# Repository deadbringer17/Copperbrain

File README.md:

# Copperbrain

Copperbrain is a local MCP server for safe KiCad 10 schematic/PCB analysis, deterministic
JLCPCB/LCSC sourcing, controlled changes, ERC/DRC validation, typed PCB design rules, and
component-only BOM estimates.

See this README for scope and public contracts, `docs/INSTALLATION.md` for setup, and
`docs/DEMO.md` for the reproducible reference flow.

## Installation

Requires Windows, Python 3.11 or newer, `uv`, and KiCad 10.x (`kicad-cli.exe` is discovered
dynamically). Controlled PCB routing uses a managed KiCadRoutingTools runtime with its
platform-specific Rust core; JLCImport and JLCPCB Tools are optional and enable local component
sourcing.

```powershell
git clone https://github.com/deadbringer17/Copperbrain.git
cd Copperbrain
uv sync --all-extras
uv run python scripts/setup_dependencies.py --skip-jlc-plugins
uv run pytest
```

Start the server with `uv run copperbrain`. Configure an MCP client to execute `uv` with arguments
`run copperbrain` and this repository as its working directory. Copperbrain exposes local stdio
only and never starts a public network listener. See `docs/INSTALLATION.md` for the full
environment-variable reference and mutation-safety details.

To update a source checkout explicitly from the official `origin/main`, run:

```powershell
uv run copperbrain update
```

The updater accepts only a clean `main` worktree with the official Copperbrain GitHub origin and
applies a Git fast-forward only. It refuses dirty worktrees, detached or different branches,
unexpected remotes, and divergent history; it never stashes, resets, rebases, or discards local
work. Restart Codex or open a new task after a successful update.

To fetch the pinned, hash-verified KiCadRoutingTools runtime and optional JLCImport/JLCPCB Tools integrations
automatically instead of installing them by hand, run:

```powershell
uv run python scripts/setup_dependencies.py
```

The script only ever contacts official sources over HTTPS (GitHub, Adoptium, `kicad.github.io`),
verifies a checksum whenever the source publishes one, and asks for confirmation before writing
anything — including the JLC plugins, which land in KiCad's own plugin directory, outside this
repository. See "Automated dependency setup" in `docs/INSTALLATION.md` for exactly what it does
and does not do.

## Installing in Codex CLI

Complete the installation above first. Codex (the `codex` CLI) reads MCP server definitions from
its `config.toml` — `~/.codex/config.toml` on Linux/macOS, `%USERPROFILE%\.codex\config.toml` on
Windows. Add a `[mcp_servers.copperbrain]` entry:

```toml
[mcp_servers.copperbrain]
command = "uv"
args = ["run", "--directory", "C:\\path\\to\\Copperbrain", "copperbrain"]
enabled = true
```

Codex launches `command` directly, without a shell and without setting a working directory of its
own, so `uv run` needs `--directory <repo>` instead of relying on `cd`; use the absolute path to
where you cloned this repository. To override an environment variable from
`docs/INSTALLATION.md#configuration` for this server only, add it under
`[mcp_servers.copperbrain.env]`, the same way other entries in `config.toml` do. Restart Codex (or
start a new session) after editing the file. Copperbrain still exposes local stdio only; registering
it this way adds no network exposure.

## Development

```powershell
uv sync --all-extras
uv run pytest
uv run ruff check .
uv run ruff format --check .
uv run mypy src
```

Run the stdio MCP server with `uv run copperbrain`.

Run the non-destructive offline demo with `uv run python scripts/run_demo.py`.

## Three acceptance gates

The public MCP exposes exactly three tools that accept a validated mutation:

1. `accept_schematic` for the project scaffold or schematic change set.
2. `accept_design_rules` for reviewed widths, clearances, vias, netclasses, and assignments.
3. `accept_pcb` for one aggregate placement, grounding, and routing change set prepared with
   `prepare_pcb_acceptance` and rechecked with `validate_pcb_acceptance`.

Granular PCB prepare/preview/validate/apply/rollback functions are internal and are not MCP tools.
They modify only the private aggregate workspace. `rollback_accepted_phase` is an explicit recovery
command, not another acceptance gate.

To start a new design safely, call `prepare_project_creation` with an existing parent directory
and a typed name/layer count. Copperbrain creates the schematic through `kicad-sch-api`, creates
the empty board through KiCad's bundled Python API, validates both files, and publishes only a
preview under `<new-project>/copperbrain-output/previews/schematic/`.
`accept_schematic` applies the validated scaffold; recovery remains hash guarded.

For an opened KiCad project, Copperbrain writes every deliverable artifact below
`<project>/copperbrain-output/`: at most the stable `schematic`, `design-rules`, and `pcb` previews
under `previews/`, plus BOM exports under `bom/`. Private mutation workspaces, caches, and rollback
snapshots are not placed in the project.

## Project analysis via MCP

Call `detect_kicad` to confirm KiCad, CLI, and JLC plugin availability, then `open_project` to
open a project read-only and hash its sources. `get_project_summary` returns sheets, components,
electrical nets, and power symbols; `analyze_schematic` returns deterministic, evidence-backed
observations; `trace_net` returns every pin KiCad assigns to one exact net name. `run_erc` and
`run_drc` run KiCad's checks and normalize violations without touching project files.

## Schematic changes via MCP

`prepare_schematic_change` stages allowlisted operations in a private workspace and returns a
semantic diff, risks, and a project-local PDF preview; `validate_change` revalidates it in place.
Applying requires the first acceptance gate, `accept_schematic`, with `confirmed=true` and
`editor_closed=true`.

## Component sourcing via MCP

`search_components` ranks JLCPCB/LCSC candidates against typed requirements using the installed
JLCPCB Tools catalog or a recorded `COPPERBRAIN_JLC_CATALOG`. `get_component_details` returns
normalized catalog details for one exact LCSC part; `compare_components` and `find_alternatives`
rank supplied or discovered candidates against the same requirements. `estimate_component_cost`
estimates component-only cost at one requested quantity. `import_component_assets` installs the
resolved symbol/footprint/3D/datasheet assets locally from allowlisted HTTPS sources.

## BOM via MCP

`generate_bom` groups and enriches the schematic BOM and writes JSON/CSV/Markdown under
`copperbrain-output/bom/`. `estimate_bom_cost` totals component-only cost at requested board
quantities; `suggest_bom_substitutions` proposes requirement-motivated alternatives for BOM lines.
All cost figures explicitly exclude PCB, assembly, stencil, shipping, taxes, and duties.

## PCB design rules via MCP

Use `analyze_pcb_constraints` to inspect current netclasses and receive evidence-backed net-role
suggestions. Pass reviewed fabrication limits and electrical intent to `propose_design_rules`,
then use `prepare_pcb_rule_change`, `validate_pcb_rule_change`, and
`accept_design_rules`. Applying requires the second acceptance and a saved, closed KiCad editor;
`rollback_accepted_phase` restores the phase snapshot when explicitly invoked.

`ManufacturingProfile` covers minimum clearance/track/via dimensions, copper thickness, allowed
temperature rise, and internal/external current layer. `NetRuleRequirement` covers exact net names,
role, current, voltage, explicit clearance/width, creepage, maximum routed length, and optional
differential geometry/maximum uncoupled length. Raw `.kicad_dru` text is never accepted through
MCP.

High-current rules require a current or reviewed width. High-voltage rules require reviewed
clearance. Differential geometry is explicitly marked as not impedance-controlled unless width
and gap are supplied from a verified stackup calculation.

Before proposing routing rules, Copperbrain resolves every connected footprint and measures its
electrical pads, minimum pitch, and edge-to-edge pad clearance. If a class width or clearance does
not fit the package, the generated `.kicad_dru` applies a narrower track width or reduced clearance
only inside that component's courtyard, never below the fabrication profile minimum. The original
class remains active outside the package. Missing project-local courtyards can be generated inside
the same previewed change set and are validated through KiCad CLI; unresolved footprints or
packages narrower than the fabrication minimum produce a safe refusal.

## PCB inspection and placement via MCP

Use `get_pcb_summary`, `inspect_pcb_net`, and `get_footprint_placement` for typed board queries.
`analyze_placement` reports conservative courtyard overlaps, footprints outside Edge.Cuts,
estimated ratsnest length, occupied envelope, compactness, side counts, and cross-layer nets.
`propose_component_placement` accepts exact references, a typed optional region, spacing/grid and
routing-corridor limits, plus deterministic `compact` or `grid`, rotation, and layer policies.
Compact placement scores pad connectivity and envelope growth, keeps connectors near edges, and
allows automatic bottom placement only for small SMD passives.

Pass the returned operations directly to `prepare_pcb_acceptance`. Placement is applied and
validated inside its private aggregate workspace without an intermediate PDF or published copy;
no separate placement preview or acceptance is exposed.

The official `kicad-python` IPC binding is installed and detected dynamically for live board
transactions. PCB inspection and safe preview do not require a running editor: the typed file
adapter and `kicad-cli` remain the deterministic offline path. No MCP placement tool accepts raw
KiCad S-expressions, and this extension does not route traces or modify zones, keepouts, or the
board outline.
Un cambio `F.Cu`/`B.Cu` viene eseguito soltanto nella copia temporanea attraverso l'API `pcbnew`
inclusa in KiCad, cosi pad, grafica, testi e modelli 3D vengono trasformati insieme. Preview, DRC,
conferma esplicita, snapshot e rollback restano obbligatori.

## Post-placement PCB grounding

Include the reviewed grounding request in `prepare_pcb_acceptance`. It targets every
pad in one or more reviewed ground domains and derives all zone outlines from the real closed
`Edge.Cuts`, pad geometry, fanouts, and vias. The default is always a two-copper-layer board:
`PGND` owns the main shaped region on `F.Cu`, while `GND` owns the main shaped region on `B.Cu`.
Planner-derived local regions on the opposite side are cut out of the main region with explicit
clearance and distinct priorities. A four-layer stackup is used only when
`copper_layers=4` is explicitly requested; that opt-in policy uses `PGND -> F.Cu/In2.Cu` and
`GND -> In1.Cu/B.Cu` for an unambiguous pair.

The domains remain distinct KiCad nets and are connected only through two-terminal bridges such as
a 0-ohm resistor or net tie explicitly named in `bridge_references`. Pads that do not touch their
assigned plane receive
typed, clearance-screened pad-to-via fanouts. `thermal` and `solid` pad connections are selectable
per domain; local shaped regions are solid and power ground commonly uses `solid`. Via-in-pad is opt-in because it requires a reviewed
fabrication process. Existing selected-net zones are replaced only when
`replace_existing_planes=true` is explicitly requested.

The result is validated inside the private aggregate workspace without a grounding preview. The
KiCad Project Manager may remain open: only a PCB document lock blocks the final aggregate
mutation. `rollback_accepted_phase` restores the aggregate PCB snapshot. Ambiguous
domain roles, overlapping layer assignments, missing/ambiguous bridges, unsafe fanouts, or new DRC
errors cause a structured refusal.
The workflow does not accept polygons or KiCad expressions from callers, and it does not claim
thermal, return-path, EMC, SI/PI, stackup, or DFM certification.

## Headless PCB initialization via MCP

For an empty board, the internal layout composer accepts a typed rectangular outline, one
placement for every physical schematic footprint, optional fixed M3 mounting holes, and explicit
footprint overrides. It synchronizes footprints, builds the unrouted PCB, and runs comparative
ERC/DRC and placement analysis inside the aggregate workspace without publishing an intermediate
preview. There is no separate layout preview or acceptance.

The bounded `test_bench_pico` reference helper demonstrates this flow for a provisional 12 V,
20 A brushed-DC H-bridge using DRV8701, four external 60 V MOSFETs, ATtiny1616, half-duplex
RS-485, and four protected 5–24 V digital sensor inputs. Its typed plan uses a compact 120 x 100 mm board,
four M3 holes, a star-separated `PGND`/logic `GND`, and a 70 um external-copper assumption. It is
a review benchmark, not a production-qualified design; high-current zones, thermal/EMC/DFM,
motor stall behavior, and the final stackup still require engineering validation.

The `benchmark_bldc_drv8311` reference project exercises the same guarded workflow on an
85 x 50 mm four-layer BLDC driver. It uses a DRV8311S integrated three-phase stage for a
provisional 9--12.6 V, 2 A continuous operating point, exposes 6-PWM, SPI, three current-sense
outputs, fault, and Hall signals, and includes input protection, decoupling, a reviewed In1.Cu GND
plane, thermal-pad via-in-pad fanout, and project-local rule classes. The generated BOM and design
report live below `benchmark_bldc_drv8311/copperbrain-output/`. It remains a benchmark, not a
production release: power/phase copper, thermal/SOA, EMC, DFM, and the remaining signal routing are
explicitly blocked by readiness evidence rather than being silently inferred.

## Controlled PCB routing via MCP

After rules and placement/grounding intent are reviewed, use `analyze_unrouted_nets`
to identify the remaining disconnected pad groups. Ground-zone connectivity is included, so the
router does not redundantly route pads already joined by an applied plane. Check
`get_routing_backend_status`, then call `propose_pcb_routing`. KiCadRoutingTools runs locally through
its Python CLI and Rust-accelerated A* core. Copperbrain can run at most three isolated ordering
strategies: `mps`, `inside_out`, and `original`. One candidate is used by default and a request for
a fourth is rejected. Copperbrain ranks candidates by completion, new DRC errors, open connections,
vias, and routed length. Only the selected candidate's copper delta becomes typed segments and vias;
there is no internal routing fallback. Reviewed planes remain on the private input board as copper
obstacles, while their nets are excluded from the explicit signal-routing batch. The selected typed
copper is applied to the already-grounded private board, followed by KiCad zone refill and
comparative DRC.
Fine-pitch escape geometry is opt-in per routing batch. When enabled, Copperbrain derives short
typed stubs from pad and courtyard geometry and, for a nearby opposite-side target, a clearance-
offset dogbone via with an outside-courtyard approach. It includes these seeds in the private router
input and subjects the resulting complete copper delta to the same scope, preservation,
connectivity, and DRC gates.
When `nets` is empty, Copperbrain materializes the exact currently-unrouted net set before starting
the backend. KiCadRoutingTools receives those exact names through its fixed `--nets` argument;
non-target nets, existing routes, planes, keepouts, pads, and the board outline remain obstacles.
Copperbrain never enables the backend option that permits ripping pre-existing routes. Every result
is rejected if it removes existing copper or adds copper outside the requested net set.

Pass the reviewed routing requests with placement and grounding to `prepare_pcb_acceptance`.
Copperbrain stops after the bounded candidate comparison, applies only the best candidate to the
private prepared PCB, refills zones, rechecks connectivity, and runs comparative DRC inside one
private workspace without routing previews. It does not keep retrying to obtain a complete route.
Final engineering cleanup and the explicit decision to apply the prepared PCB remain with the
user. Only the complete aggregate publishes
`copperbrain-output/previews/pcb/` and can be applied by `accept_pcb` with the third acceptance and
a closed editor. The KiCad Project Manager may remain open; only a PCB-document lock blocks the
aggregate apply/rollback. Boards containing pre-existing copper are rejected by default; explicitly select the
`preserve` policy only for intentional incremental routing. Wall-time and output-stall watchdogs
stop the complete router process tree. The typed delta is always applied to the original-precision
project copy.
Each proposal writes versioned baseline and per-candidate JSON metrics below the private
`COPPERBRAIN_DATA_DIR/metrics/connectivity/` tree. KiCadRoutingTools attempt records retain bounded
queued/routed/failure counts, duration, routed copper, watchdog evidence, and resource data when the
backend exposes it. Backend output is bounded and sensitive net names are replaced with hashes. The returned
`RoutingPlan.metrics_run_id` correlates those records with preview, apply, and recovery.
Call `get_connectivity_metrics` with that ID for a bounded, sanitized optimization view including
the best observed pass, connection delta, failed-candidate count, stagnation, and watchdog causes.
New records use schema 5 while the reader remains compatible with persisted schema-2 records.

For the compact end-to-end surface, call `prepare_pcb_acceptance`, review its preview, then use
`validate_pcb_acceptance` and `accept_pcb`. `assess_pcb_readiness` intentionally keeps
`production_ready=false` when DFM, stackup,
thermal, SI/PI, EMC, or impedance checks have not been performed, even if routing/ERC/DRC pass.

The AI may explain and review the structured candidate evidence, but it cannot override
connectivity, DRC, confirmation, stale-hash, or editor-state gates. This workflow does not certify
impedance, SI/PI/EMC, thermal behavior, or regulatory compliance. Raw KiCad expressions, zones,
and keepouts remain unavailable through the routing tools.

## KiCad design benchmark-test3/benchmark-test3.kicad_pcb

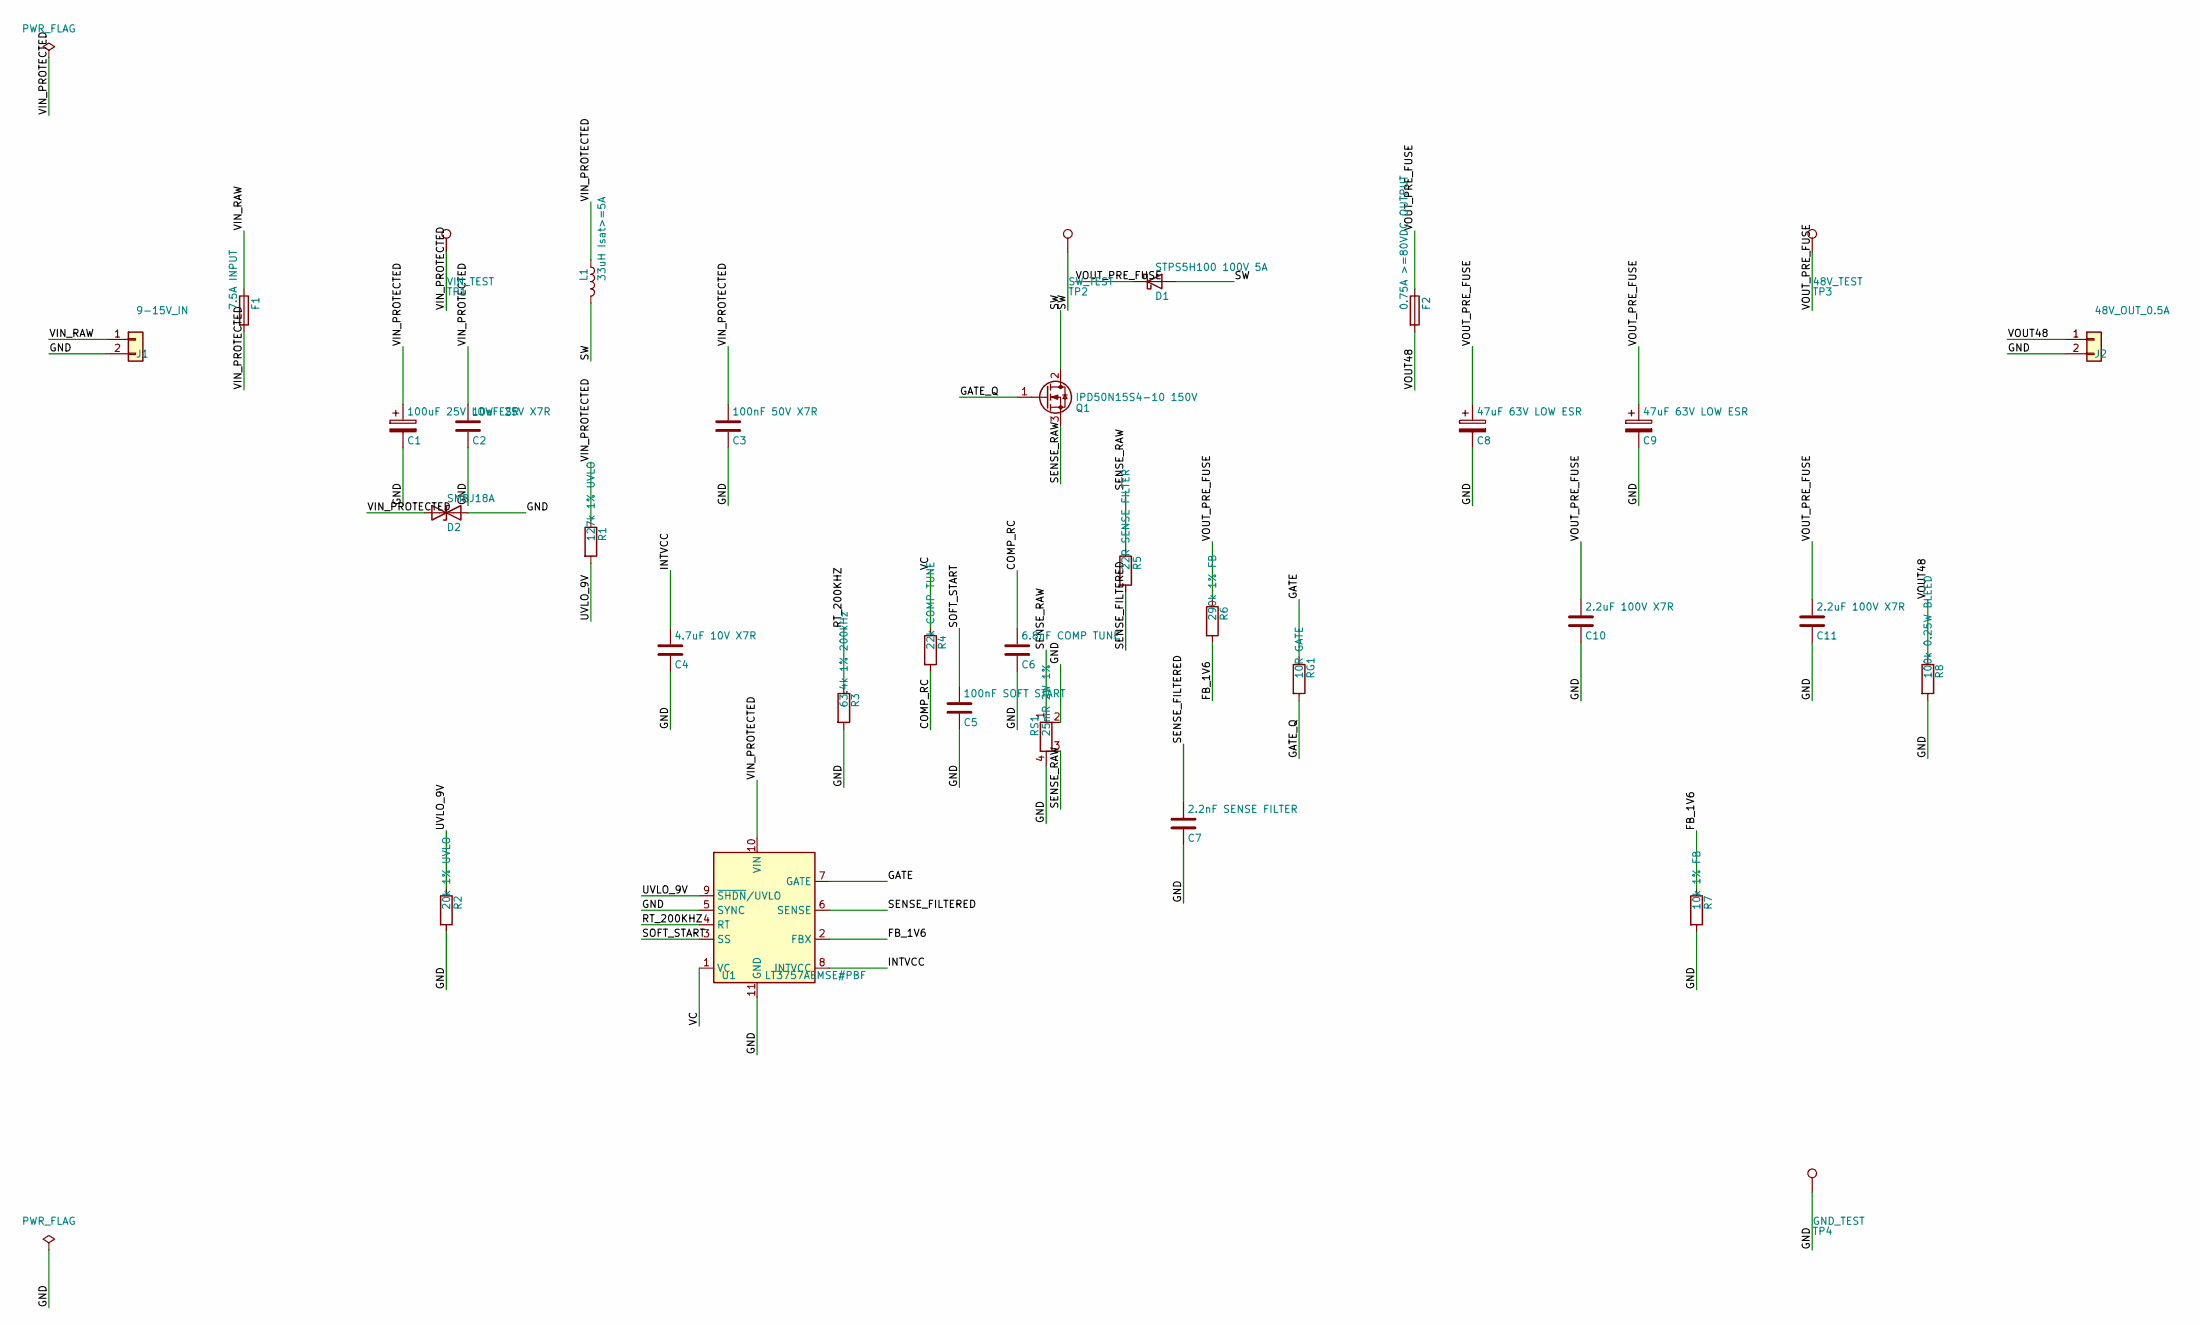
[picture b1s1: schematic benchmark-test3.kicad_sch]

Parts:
C1: 100uF 25V LOW ESR; CP_Elec_8x10
C2: 10uF 25V X7R; C_1210_3225Metric
C3: 100nF 50V X7R; C_0805_2012Metric
C4: 4.7uF 10V X7R; C_0805_2012Metric
C5: 100nF SOFT START; C_0603_1608Metric
C6: 6.8nF COMP TUNE; C_0603_1608Metric
C7: 2.2nF SENSE FILTER; C_0603_1608Metric
C8, C9: 47uF 63V LOW ESR; CP_Elec_10x10.5
C10, C11: 2.2uF 100V X7R; C_1210_3225Metric
D1: STPS5H100 100V 5A; TO-252-3_TabPin2
D2: SMBJ18A; D_SMB
F1: 7.5A INPUT; Fuse_1812_4532Metric
F2: 0.75A >=80VDC OUTPUT; Fuse_1206_3216Metric
J1: 9-15V_IN; TerminalBlock_MaiXu_MX126-5.0-02P_1x02_P5.00mm
J2: 48V_OUT_0.5A; TerminalBlock_MaiXu_MX126-5.0-02P_1x02_P5.00mm
L1: 33uH Isat>=5A; L_Coilcraft_MSS1260-XXX
Q1: IPD50N15S4-10 150V; TO-252-3_TabPin2
R1: 127k 1% UVLO; R_0805_2012Metric
R2: 20k 1% UVLO; R_0805_2012Metric
R3: 63.4k 1% 200kHz; R_0603_1608Metric
R4: 22k COMP TUNE; R_0603_1608Metric
R5: 22R SENSE FILTER; R_0603_1608Metric
R6: 290k 1% FB; R_0805_2012Metric
R7: 10k 1% FB; R_0805_2012Metric
R8: 100k 0.25W BLEED; R_1206_3216Metric
RG1: 10R GATE; R_0603_1608Metric
RS1: 25mR 2W 1%; R_Shunt_Vishay_WSK2512_6332Metric_T2.21mm
TP1: VIN_TEST; TestPoint_Plated_Hole_D2.0mm
TP2: SW_TEST; TestPoint_Plated_Hole_D2.0mm
TP3: 48V_TEST; TestPoint_Plated_Hole_D2.0mm
TP4: GND_TEST; TestPoint_Plated_Hole_D2.0mm
U1: LT3757AEMSE#PBF; MSOP-10-1EP_3x3mm_P0.5mm_EP1.68x1.88mm; MPN LT3757AEMSE#PBF

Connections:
/COMP_RC: C6.1, R4.2
/FB_1V6: R6.2, R7.1, U1.2 (FBX)
/GATE: RG1.1, U1.7 (GATE)
/GATE_Q: Q1.1 (G), RG1.2
/GND: C1.2, C2.2, C3.2, C4.2, C5.2, C6.2, C7.2, C8.2, C9.2, C10.2, C11.2, D2.2 (A2), J1.2, J2.2, R2.2, R3.2, R7.2, R8.2, RS1.2, RS1.4, TP4.1, U1.5 (SYNC), U1.11 (GND)
/INTVCC: C4.1, U1.8 (INTVCC)
/RT_200KHZ: R3.1, U1.4 (RT)
/SENSE_FILTERED: C7.1, R5.2, U1.6 (SENSE)
/SENSE_RAW: Q1.3 (S), R5.1, RS1.1, RS1.3
/SOFT_START: C5.1, U1.3 (SS)
/SW: D1.2 (A), L1.2, Q1.2 (D), TP2.1
/UVLO_9V: R1.2, R2.1, U1.9 (~SHDN/UVLO)
/VC: R4.1, U1.1 (VC)
/VIN_PROTECTED: C1.1, C2.1, C3.1, D2.1 (A1), F1.2, L1.1, R1.1, TP1.1, U1.10 (VIN)
/VIN_RAW: F1.1, J1.1
/VOUT48: F2.2, J2.1, R8.1
/VOUT_PRE_FUSE: C8.1, C9.1, C10.1, C11.1, D1.1 (K), F2.1, R6.1, TP3.1

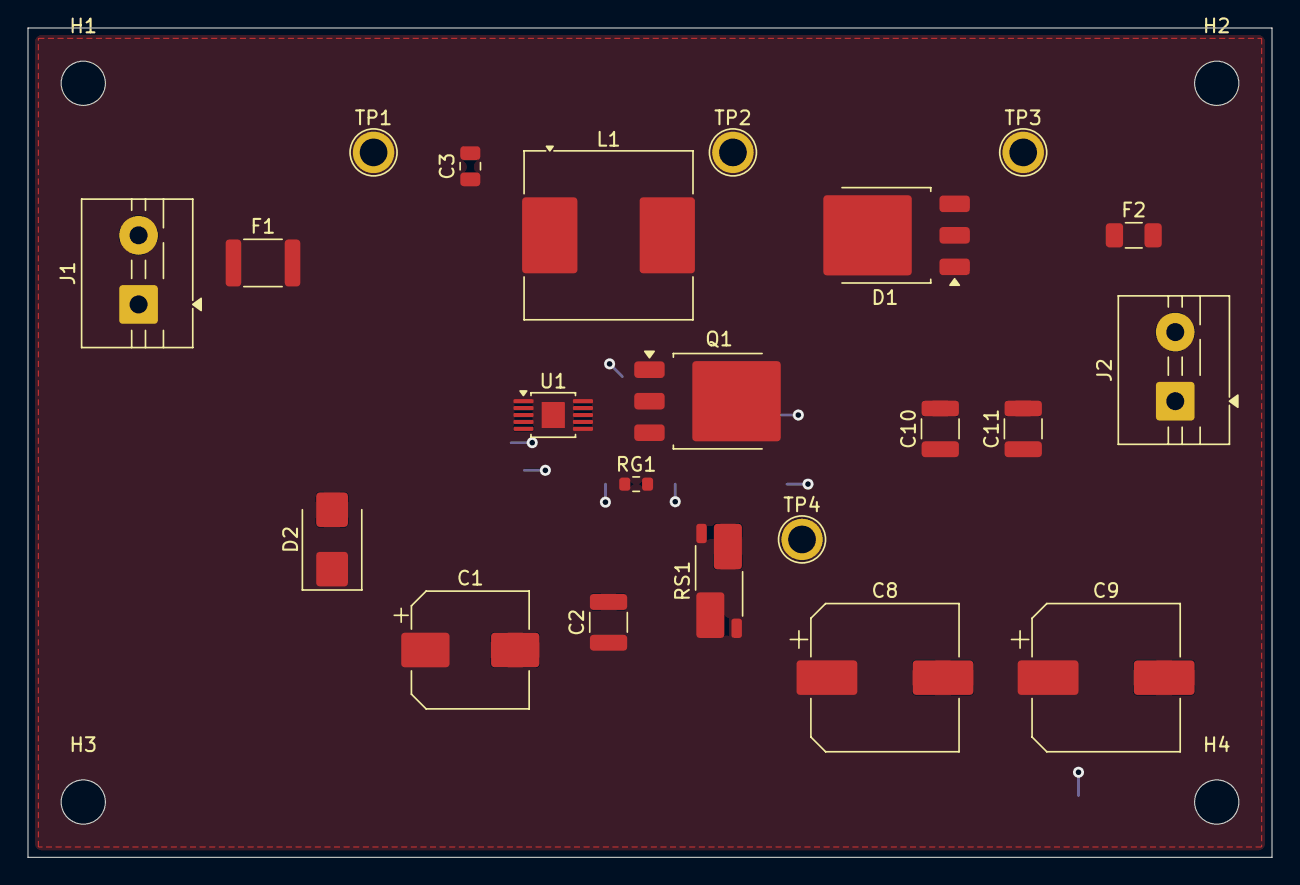
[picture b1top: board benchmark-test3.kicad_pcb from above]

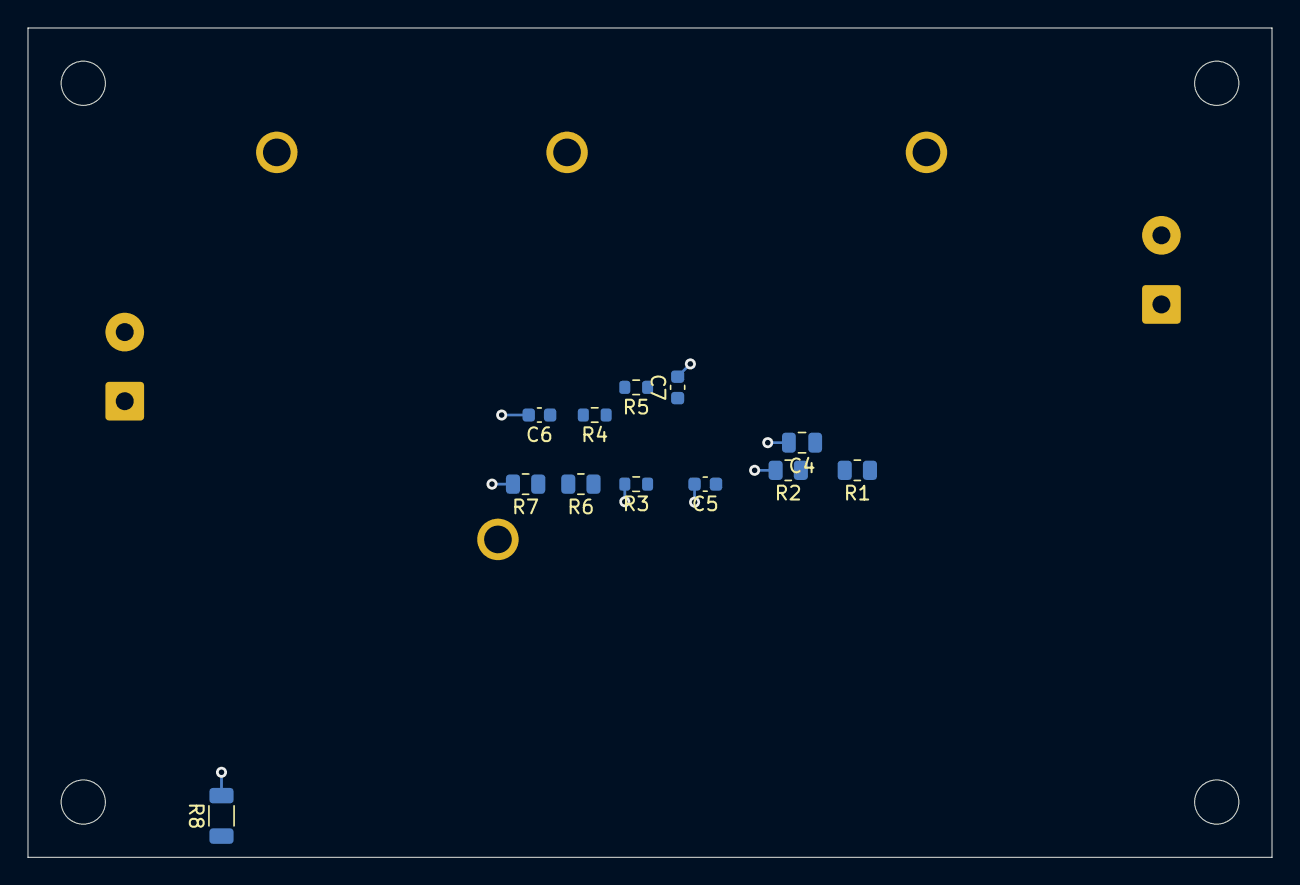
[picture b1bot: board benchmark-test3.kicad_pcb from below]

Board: 2 copper layers, 90.0 x 60.0 mm, 38 parts (12 on the bottom side), 17 nets.

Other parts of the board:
H1, H2, H3, H4: MountingHole_3.2mm_M3

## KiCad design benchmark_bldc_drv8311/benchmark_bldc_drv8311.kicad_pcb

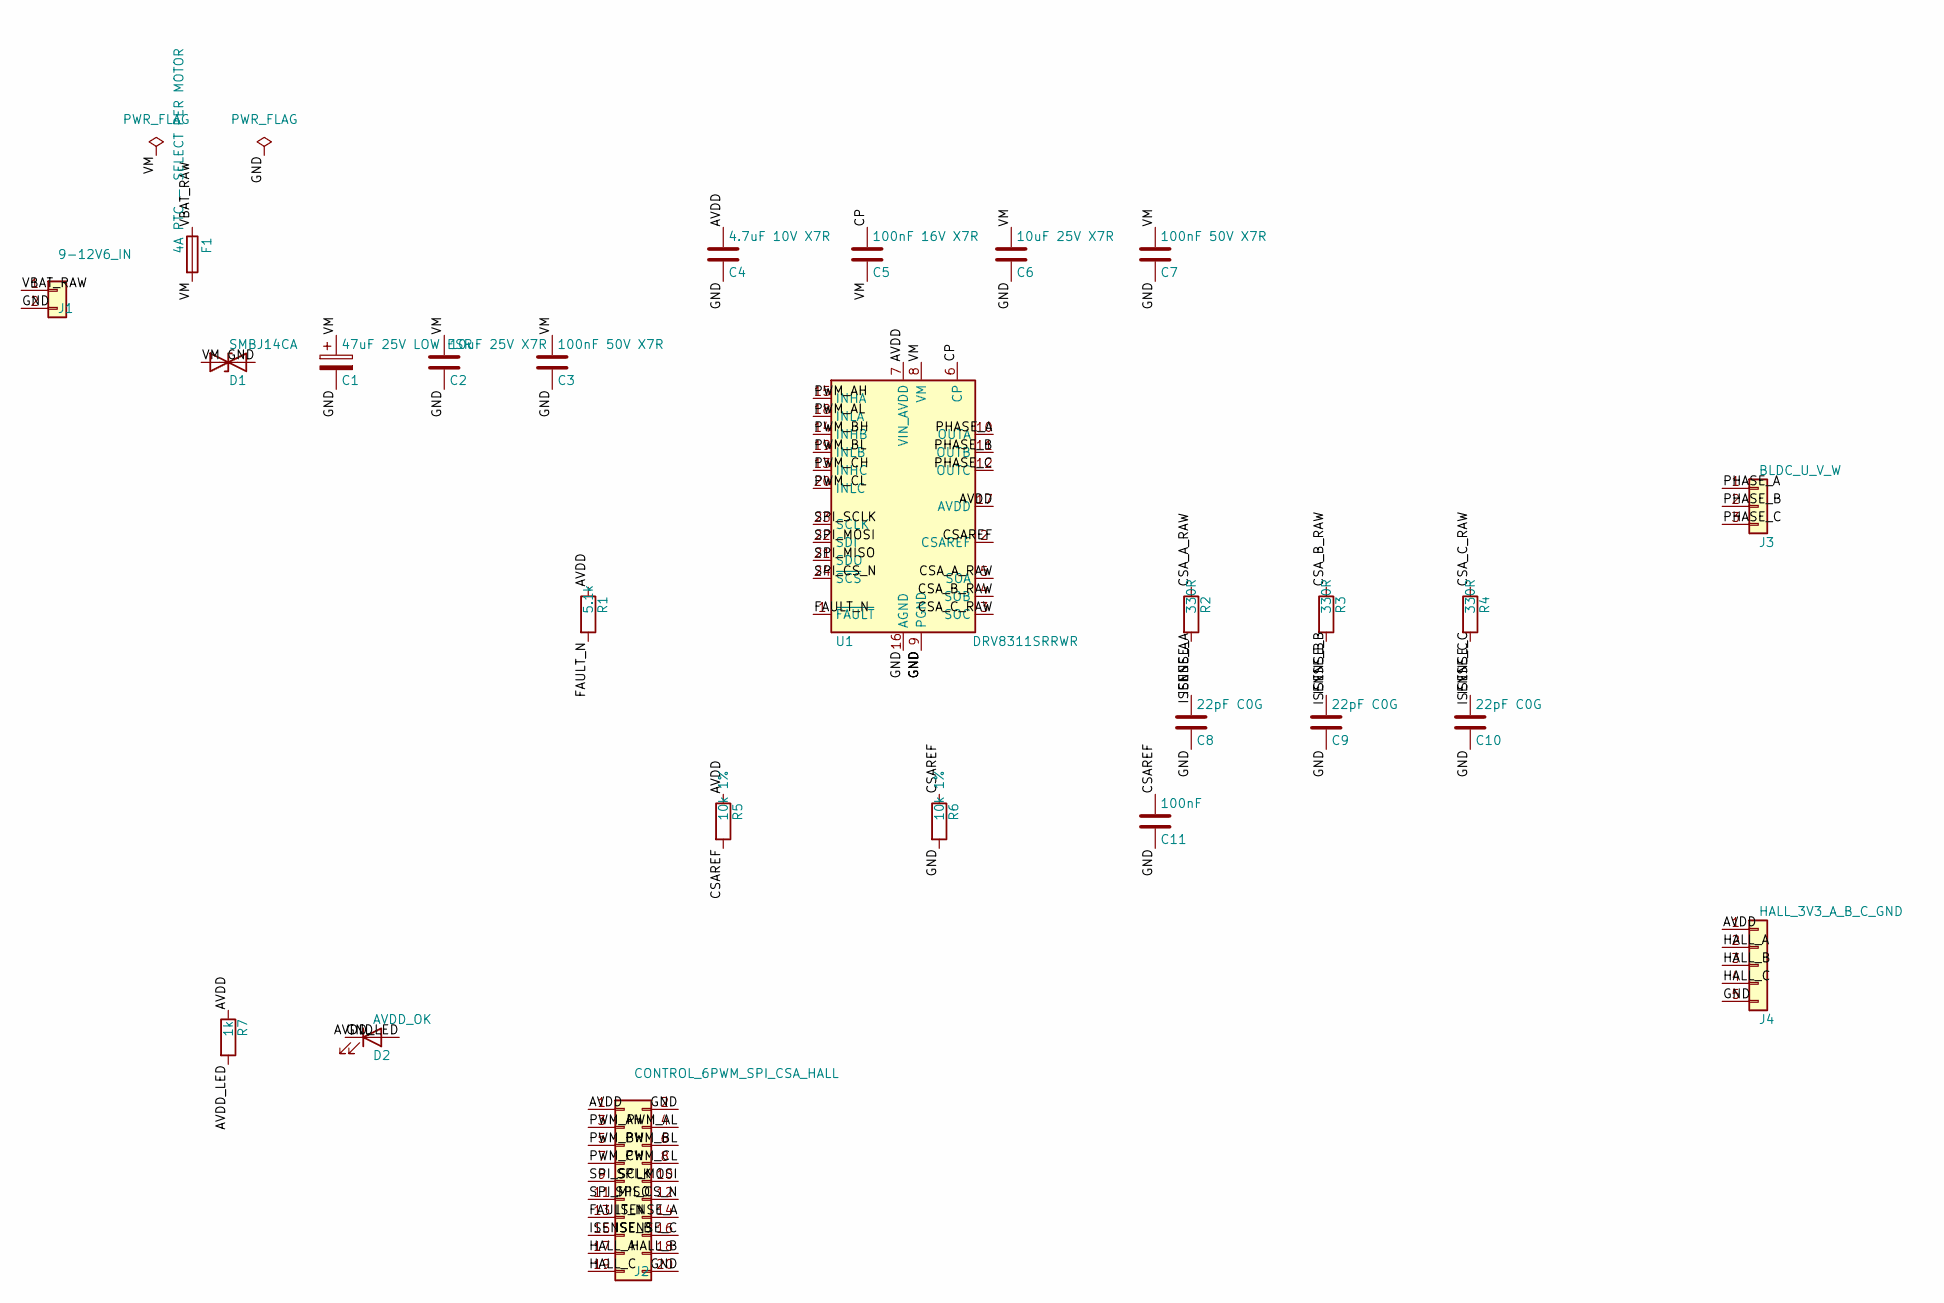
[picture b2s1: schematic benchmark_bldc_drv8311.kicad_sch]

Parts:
C1: 47uF 25V LOW ESR; CP_Radial_D8.0mm_P3.50mm
C2, C6: 10uF 25V X7R; C_1206_3216Metric
C3, C7: 100nF 50V X7R; C_0603_1608Metric
C4: 4.7uF 10V X7R; C_0805_2012Metric
C5: 100nF 16V X7R; C_0603_1608Metric
C8, C9, C10: 22pF C0G; C_0603_1608Metric
C11: 100nF; C_0603_1608Metric
D1: SMBJ14CA; D_SMB; MPN SMBJ14CA; LCSC C151253
D2: AVDD_OK; LED_0603_1608Metric
F1: 4A PTC - SELECT PER MOTOR; Fuse_1812_4532Metric_Pad1.30x3.40mm_HandSolder
J1: 9-12V6_IN; TerminalBlock_MaiXu_MX126-5.0-02P_1x02_P5.00mm
J2: CONTROL_6PWM_SPI_CSA_HALL; PinHeader_2x10_P1.27mm_Vertical
J3: BLDC_U_V_W; TerminalBlock_MaiXu_MX126-5.0-03P_1x03_P5.00mm
J4: HALL_3V3_A_B_C_GND; JST_PH_B5B-PH-K_1x05_P2.00mm_Vertical
R1: 5.1k; R_0603_1608Metric
R2, R3, R4: 330R; R_0603_1608Metric
R5, R6: 10k 1%; R_0603_1608Metric
R7: 1k; R_0603_1608Metric
U1: DRV8311SRRWR; Texas_RRW0024A_WQFN-24-1EP_3x3mm_P0.4mm_EP1.9x1.9mm; MPN DRV8311SRRWR; LCSC UNSOURCED

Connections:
/AVDD: C4.1, J2.1, J4.1, R1.1, R5.1, R7.1, U1.7 (VIN_AVDD), U1.17 (AVDD)
/AVDD_LED: D2.2 (A), R7.2
/CP: C5.1, U1.6 (CP)
/CSAREF: C11.1, R5.2, R6.1, U1.2 (CSAREF)
/CSA_A_RAW: R2.1, U1.5 (SOA)
/CSA_B_RAW: R3.1, U1.4 (SOB)
/CSA_C_RAW: R4.1, U1.3 (SOC)
/FAULT_N: J2.13, R1.2, U1.1 (~FAULT)
/GND: C1.2, C2.2, C3.2, C4.2, C6.2, C7.2, C8.2, C9.2, C10.2, C11.2, D1.2 (A2), D2.1 (K), J1.2, J2.2, J2.20, J4.5, R6.2, U1.9 (PGND), U1.16 (AGND), U1.25 (PGND)
/HALL_A: J2.17, J4.2
/HALL_B: J2.18, J4.3
/HALL_C: J2.19, J4.4
/ISENSE_A: C8.1, J2.14, R2.2
/ISENSE_B: C9.1, J2.15, R3.2
/ISENSE_C: C10.1, J2.16, R4.2
/PHASE_A: J3.1, U1.10 (OUTA)
/PHASE_B: J3.2, U1.11 (OUTB)
/PHASE_C: J3.3, U1.12 (OUTC)
/PWM_AH: J2.3, U1.15 (INHA)
/PWM_AL: J2.4, U1.18 (INLA)
/PWM_BH: J2.5, U1.14 (INHB)
/PWM_BL: J2.6, U1.19 (INLB)
/PWM_CH: J2.7, U1.13 (INHC)
/PWM_CL: J2.8, U1.20 (INLC)
/SPI_CS_N: J2.12, U1.24 (~SCS)
/SPI_MISO: J2.11, U1.21 (SDO)
/SPI_MOSI: J2.10, U1.22 (SDI)
/SPI_SCLK: J2.9, U1.23 (SCLK)
/VBAT_RAW: F1.1, J1.1
/VM: C1.1, C2.1, C3.1, C5.2, C6.1, C7.1, D1.1 (A1), F1.2, U1.8 (VM)

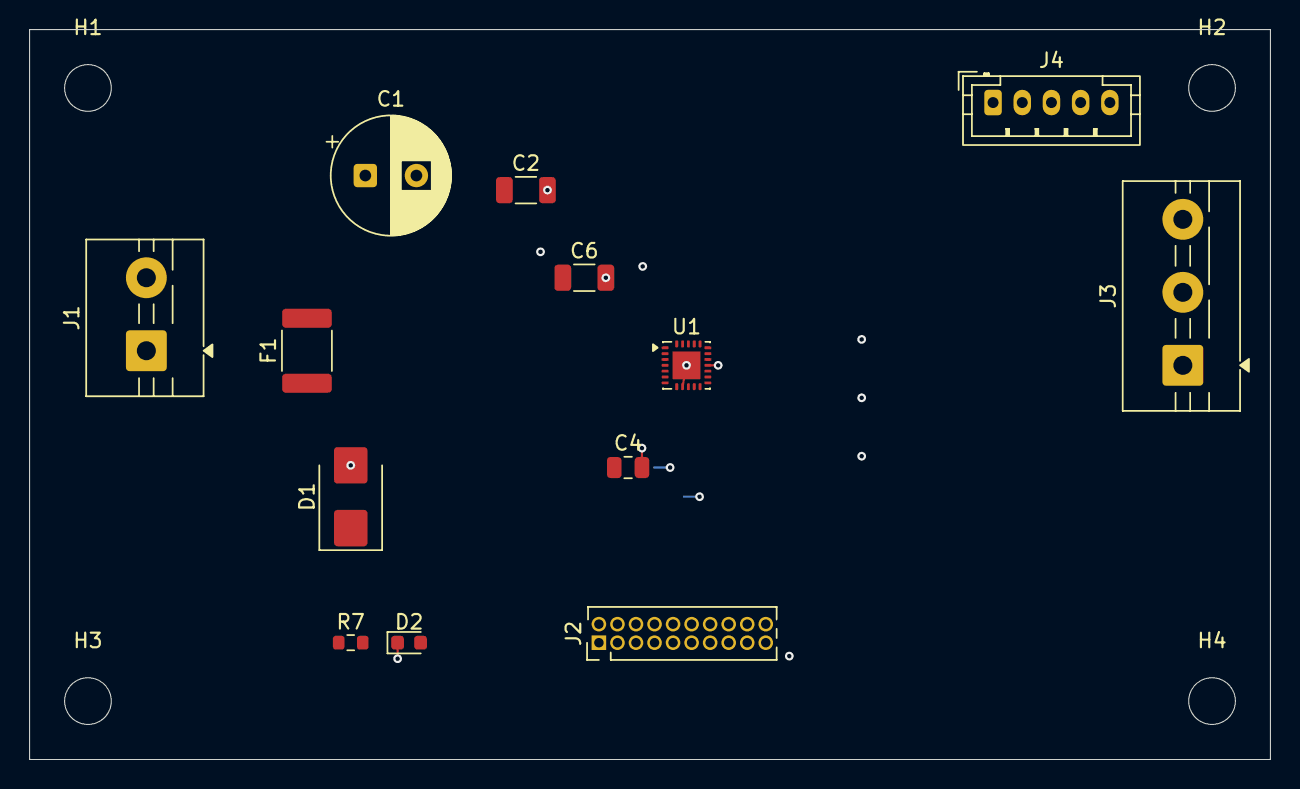
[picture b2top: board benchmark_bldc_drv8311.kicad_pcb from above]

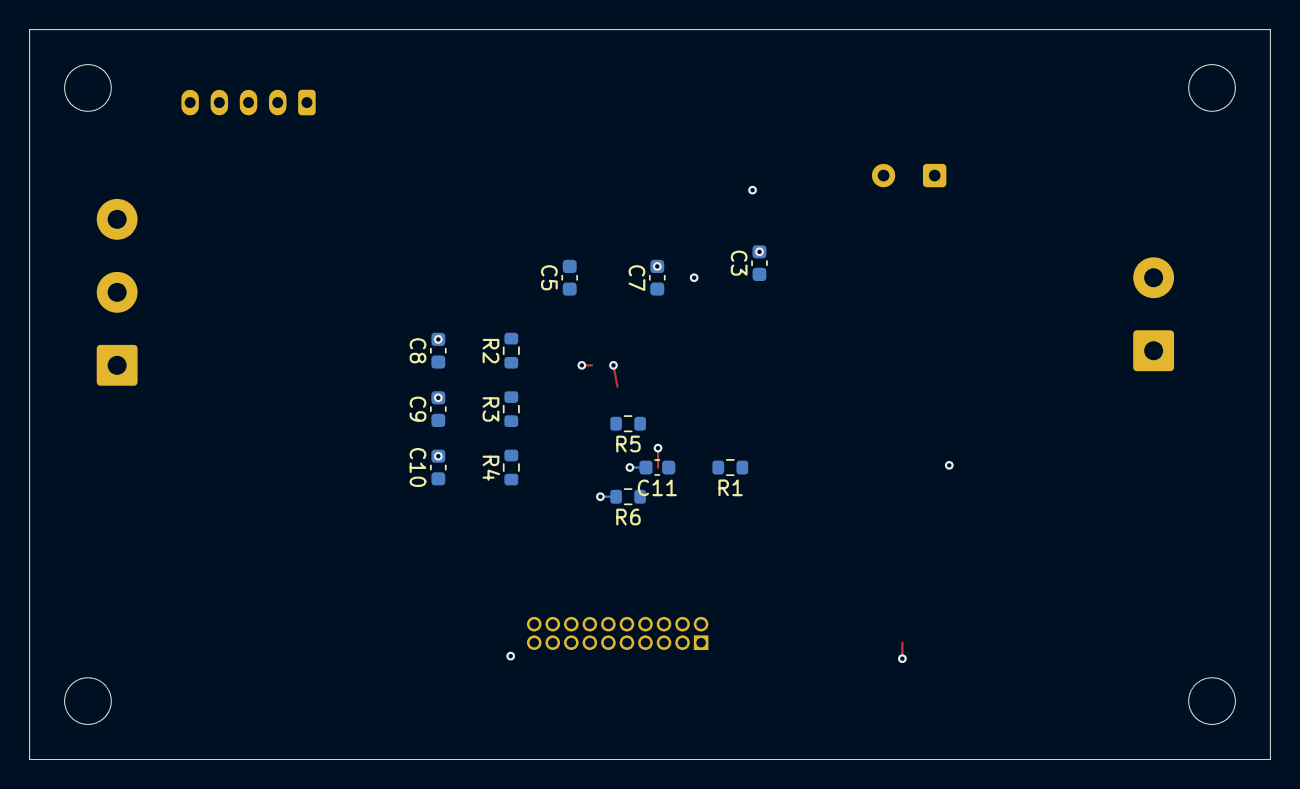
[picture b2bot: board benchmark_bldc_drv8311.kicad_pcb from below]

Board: 4 copper layers, 85.0 x 50.0 mm, 30 parts (13 on the bottom side), 30 nets.

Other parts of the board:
H1, H2, H3, H4: MountingHole_3.2mm_M3
